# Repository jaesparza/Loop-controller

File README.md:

# Loop antenna tunning control <br>

> - High voltage and currents can develop in an efficient loop antenna. If not properly constructed, lethal currents could be derived to your control board.  
> - I make no claims with regards to RF safety, EMC compatibility or compliance to standards of any kind.
> - This is a home-made prototype for hobby applications, you (as potential builder) are solely responsible for your actions.

This project implements a tunning control system for magnetic loop antennas. The antenna is tunned by turning a variable capacitor through a stepper motor at reduced speeds. The controller generates the step signals to be provided to the driver, allows movement only within the specified limits and handles the user interface.

Main characteristics:
- Configurable speeds for fast and slow operation.
- Support for stepper motors of different pulses per rotation and with planetary reductions.
- Smooth stepper motor rotation through microstepping.
- Movement limitation based on discrete step counts or on encoder readings via ADC.

This repository hosts:
- Design calculations
- Hardware designs: schematic, PCB layouts and Gerbers ready to upload for production
- Software implementation of a reconfigurable controller to operate vacuum and butterfly capacitors, with different rotation limit control strategies.
- Notes on mechanical aspects and component selection.

The repository hosts two prototypes: a wired and a wireless control system. As of today only the wired system is complete.

## Wired control - Completed and deployed

| [Software](https://github.com/jaesparza/Loop-controller/tree/master/Software/tunerControllerGen1) | 
[Hardware](https://github.com/jaesparza/Loop-controller/tree/master/pcb/initialPrototype) |

This is a working system relying on a wired connection to deliver motor coil currents as well as reading back the encoder position.

The user interface is implemented through:
- a 16x2 LCD screen to display current capacitor position with a bar and a count,
- two push buttons to trigger clockwise or counter-clockwise rotations,
- a switch to select fast or slow speed.

In my implementation I use an ethernet network cable to be run in parallel with the coaxial cable carrying the RF singal. I have not experienced problems with electrical noise or spurious readings in the ADC due to long cable runs.

## Wireless control - Prototype, on hold
Currently under development, this second version of the controller features wireless control over 802.15.4. The remote control board is intended to be placed together with the antenna in the remote location. The user interacts with the control through a PC application.

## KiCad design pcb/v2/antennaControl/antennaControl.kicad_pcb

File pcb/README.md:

# Hardware notes

Fixes:

* **Pull-up fix in the enable motor stepper controller signal**  it is important to add a 1 kOhm pull-up to the enable signal so it has a defined state when the microcontroller is going through a power-on/reset. It can be added easily on the back of the PCB between the *Enable* and the *Vcc* pins.

## Wired control board
- Only revB of the PCB is available in here, revA had routing problems and was discarded in the design tool.
- The hardware was developed with easyEDA and I used JLPCB for production.

## Wireless control board
- The hardware was developed with KiCAD and I used JLPCB for production.

Misc. notes:
- Power through LiPo battery - solar panel could be used.
- The control board runs at 3V to reduce power consumption and to avoid level shifters to interface peripherals. Software is currently under development.

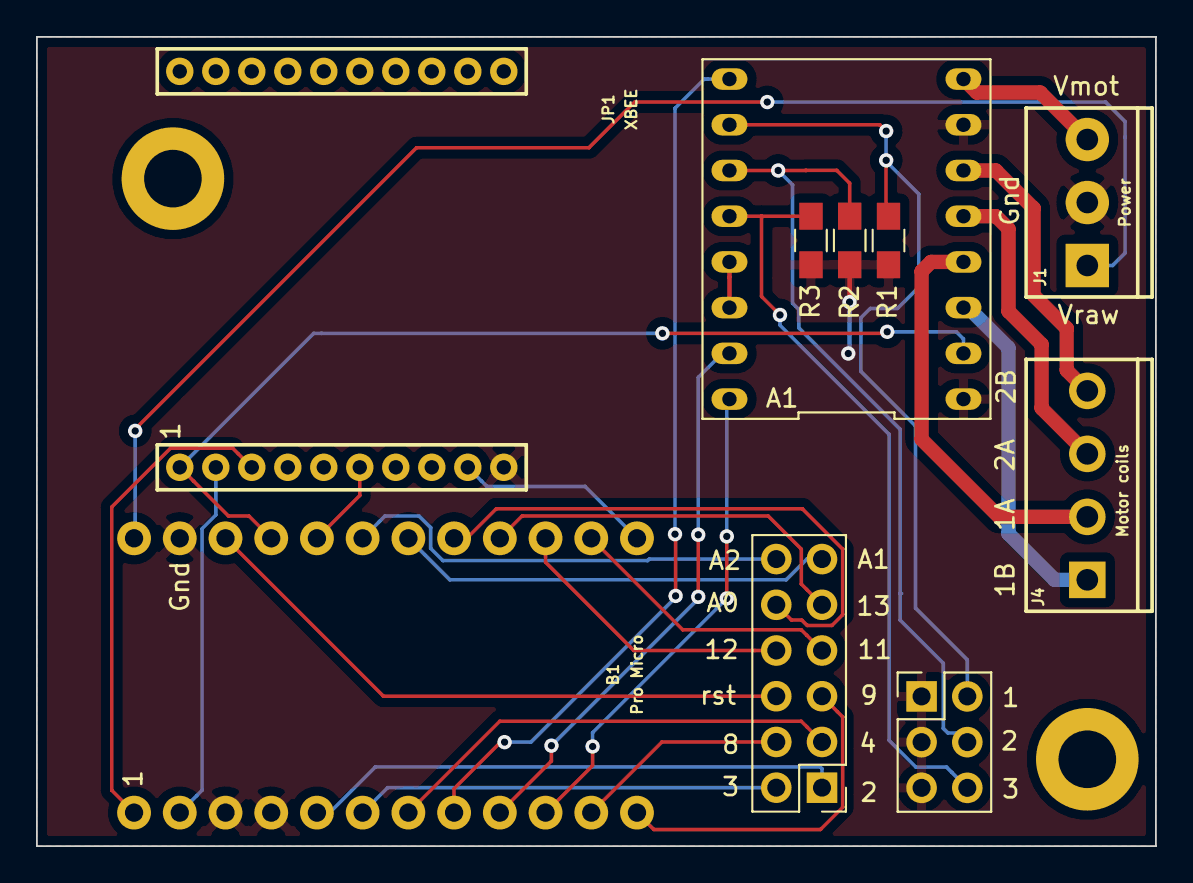
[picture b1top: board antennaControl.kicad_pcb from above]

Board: 2 copper layers, 62.2 x 45.0 mm, 12 parts (0 on the bottom side), 31 nets.

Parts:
A1: Breakout_A4988; Pololu_Breakout_4988
B1: Pro Micro; SPARKFUN_PRO_MICRO
J1: Power; SCREWTERMINAL-3.5MM-3
J2: GPIOS; Pin_Header_Straight_2x06_Pitch2.54mm
J3: Microstepping; Pin_Header_Straight_2x03_Pitch2.54mm
J4: Motor coils; SCREWTERMINAL-3.5MM-4
JP1: XBEE
R1, R2, R3: 10K; R_0805_HandSoldering
REF1: M3_2; MountingHole_3.2mm_M3_ISO7380_Pad
REF2: M3_1; MountingHole_3.2mm_M3_ISO7380_Pad

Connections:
/2: B1.5, J2.1
/3: B1.6, J2.2
/4: B1.7, J2.3
/8: B1.11, J2.4
/9: B1.12, J2.5
/10: B1.13, JP1.9
/11: B1.14, J2.7
/12: B1.15, J2.8
/13: B1.16, J2.9
/A0: B1.17, J2.10
/A1: B1.18, J2.11
/A2: B1.19, J2.12
/A3: B1.20, JP1.6
Direction: A1.16, B1.10
Enable: A1.9, B1.8
GND: A1.1, A1.7, B1.3, B1.4, B1.23, J1.2, J3.1, J3.3, J3.5, JP1.10, R1.2, R2.2, R3.2
unnamed: A1.3, J4.1
unnamed: A1.4, J4.2
unnamed: A1.5, J4.3
unnamed: A1.6, J4.4
unnamed: A1.10, J3.2, R1.1
unnamed: A1.11, J3.4, R2.1
unnamed: A1.12, J3.6, R3.1
unnamed: A1.13, A1.14
unnamed: B1.24, J1.1
RX: B1.2, JP1.2
Reset: B1.22, J2.6
Step: A1.15, B1.9
TX: B1.1, JP1.3
Vcc: A1.2, B1.21, JP1.1
Vmot: A1.8, J1.3

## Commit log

2018-05-05 :confetti_ball: Added .gitattributes & .gitignore files
2018-06-16 Added sloeber project
2018-06-17 Removed initial eclipse project
2018-06-17 Adding full eclipse project
2018-06-17 Removed sloeber dependent files
2019-05-30 Control board v2
    Control board v2 revA
2019-05-30 Added gerbers
2019-05-31 Regenerated production files
    Regenerated production files since I was missing soldering mask layers
2019-05-31 Added initial prototype design and production files
2019-06-03 Added exported schematic to pdf
2019-12-15 Added structure for actions file
2020-02-05 Create tunnerControllerMKII.ino
    Initial hack to get the motor moving remotely.
2020-02-05 Added hardware definition header file.
2020-04-13 Separated functionality and improved bar display
2020-04-13 Added statics
2020-04-13 LCD code refactored and progress bar added
    Tested with a 400 steps motor
2020-04-13 Added two configurations, fixed a rev counting bug
2020-04-27 Added refactored tunnerController for v1 PCB
2020-04-29 Reformatting and added .clang_format file
2020-04-29 Created Singleton for Input class
2020-04-29 Remove comment with link
2020-04-29 Replaced byte type with uint8_t
2020-04-29 Added Singletos for StepperMotor and UI classes
2020-04-29 Scope resolution and typo fix
2020-04-29 Wrapped operation and configuration methods in separate classes
2020-04-29 Replaced showMode with showText
2020-04-29 Placed todos
2020-04-29 Include tide-up
2020-04-29 Re-structured code base
2020-04-29 New movement parameters for the 400 steps motor
2020-04-30 Table trimming
2020-04-30 Deprecated initial prototype
2020-04-30 Corrected immediate update functionality to count steps correctly
2020-04-30 Extracted display update logic
2020-04-30 Added stub for EEPROM access
2020-04-30 Added storage of capacitor position in NVRAM
2020-04-30 Corrected detection of pushbutton press
2020-04-30 Updated pending improvements
2020-05-01 Added documentation folder with datasheets and links
2020-05-01 Renamed so GitHub renders it upon load
2020-05-01 Added new temporal configuration for the vacuum capacitor assembly
2020-05-01 Create LICENSE
2020-05-03 Extended the number of counts and added DECIMATE option
    This allows to operate motors with large reductions and still keep track of a maximum number of steps while. DECIMATE allows to divide the total count to create an approximate position representation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
2020-05-08 Added jupyter notebook file with design calculations
2020-05-09 Added formulas to calculate AC resistance
2020-05-09 Added misc equations and calcuation of the ditributed capacitance
2020-05-18 Added decimate parameter to description
2020-05-18 Added softlimits to the stepper motor movement.
2020-05-18 Added description of softlimits parameters.
2020-05-21 Added softlimit override via define
2020-05-21 Removed old configuration parameter
2020-09-20 Added ADC definition and file
2020-09-20 Include ADC and calibration routine using it
2020-09-20 Calibrate mods
2020-09-21 Renamed ADC.h to Encoder.h
2020-09-22 Added new hardware configuration, renamed ADC input
2020-09-22 Refactored operate motor method
2020-09-22 Added operation mode
2020-09-24 Simplified configuration and removed dependency to eeprom
2020-09-25 Added compilation switches for difference configurations
2020-10-09 Added the RJ45 breakout board
2021-04-15 Create arduino.json
    VS code configuration to compile and upload to arduino board pro micro
2021-05-01 Added new active configuration
2021-05-01 Added new character definitions
2021-05-01 Added functionality to update position bar according to encoder readings
2021-05-01 Removed CI Badge
2022-02-12 Collection of measurements for 20 to 10m bands
2022-02-12 Analyzer snapshots
2022-02-12 Moved measurements
2022-02-12 Added placeholder for second set of measurements
2022-02-14 Added plotting scripts
2022-03-26 plotting scripts moved to folder
2022-03-26 Moved old files to dedicated folder
2022-03-26 Updated measurement plan
2022-03-27 Created description for the measurement folder.
2022-04-01 New batch of measurements
2022-04-01 Folder rename
2022-04-06 Plot scripts modified and using the new measurements

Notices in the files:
README.md:
License: GPL v2
